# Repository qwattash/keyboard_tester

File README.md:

# Components for testing an early prototype RGB backlit keyboard

The design is based on the atmega32u4 MCU, found on teensey boards and arduino Leonardo boards, and an ISSI 3733 led driver that can drive leds for half of a full-size keyboard.

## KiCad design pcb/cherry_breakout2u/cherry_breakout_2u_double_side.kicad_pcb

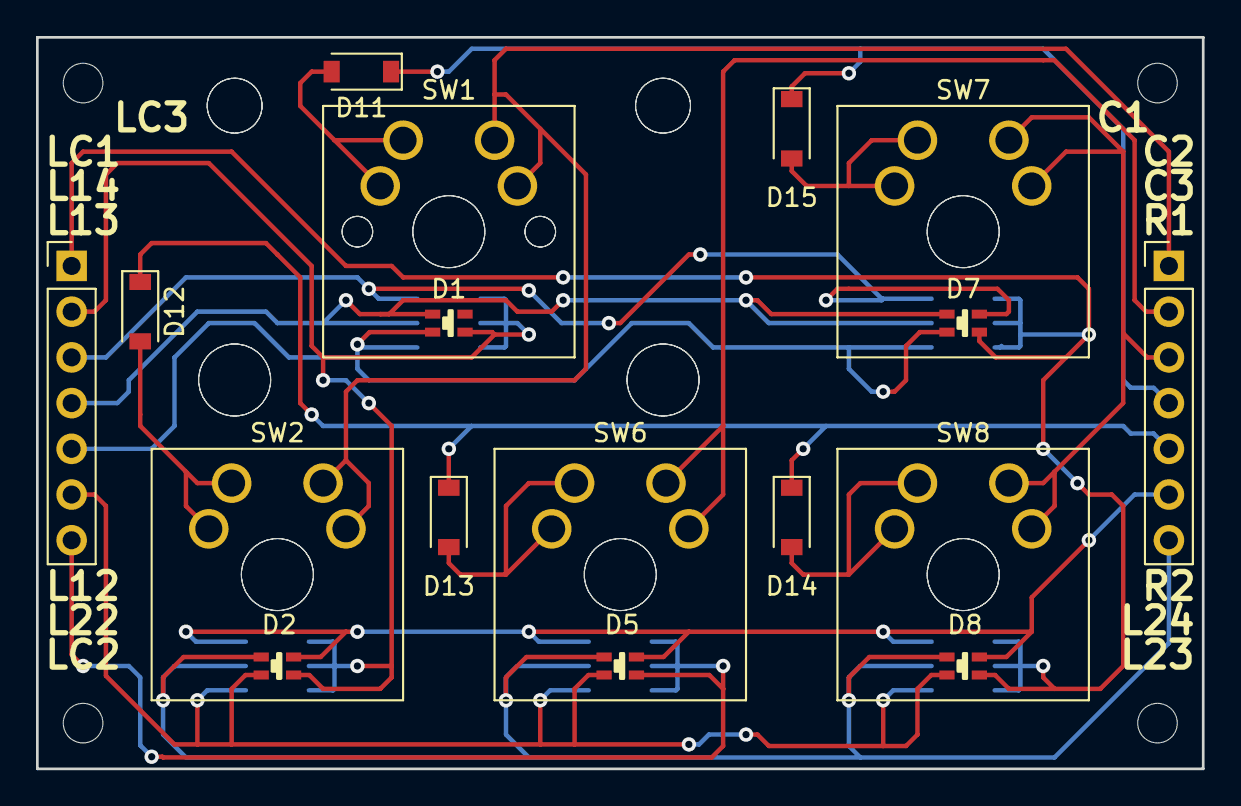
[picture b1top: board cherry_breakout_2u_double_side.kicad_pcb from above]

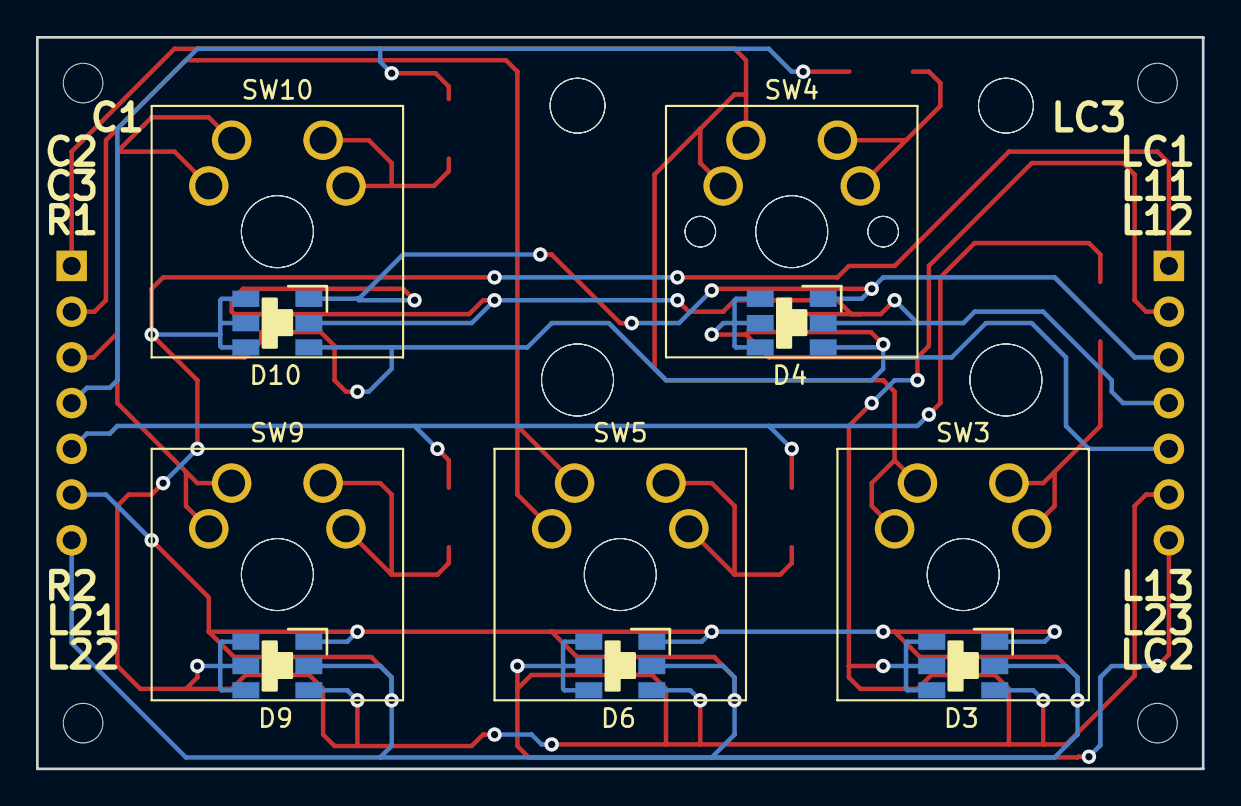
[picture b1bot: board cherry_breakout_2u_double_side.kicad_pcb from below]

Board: 2 copper layers, 64.8 x 40.6 mm, 27 parts (10 on the bottom side), 19 nets.

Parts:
D1: LED_A; Led_SMD_0606
D2: LED_C; Led_SMD_0606
D3: LED_Cb; LED_smd_1214
D4: LED_Ab; LED_smd_1214
D5: LED_D; Led_SMD_0606
D6: LED_Db; LED_smd_1214
D7: LED_B; Led_SMD_0606
D8: LED_E; Led_SMD_0606
D9: LED_Eb; LED_smd_1214
D10: LED_Bb; LED_smd_1214
D11: D_A; D_SOD-123
D12: D_C; D_SOD-123
D13: D_D; D_SOD-123
D14: D_E; D_SOD-123
D15: D_B; D_SOD-123
J1: ConnLeft; Pin_Header_Straight_1x07_Pitch2.54mm
J2: ConnRight; Pin_Header_Straight_1x07_Pitch2.54mm
SW1: A; SW_Cherry_MX1A_2.00u_PCB
SW2: C; SW_Cherry_MX1A_1.00u_Plate
SW3: Cb; SW_Cherry_MX1A_1.00u_Plate
SW4: Ab; SW_Cherry_MX1A_2.00u_PCB
SW5: Db; SW_Cherry_MX1A_1.00u_Plate
SW6: D; SW_Cherry_MX1A_1.00u_Plate
SW7: B; SW_Cherry_MX1A_1.00u_Plate
SW8: E; SW_Cherry_MX1A_1.00u_Plate
SW9: Eb; SW_Cherry_MX1A_1.00u_Plate
SW10: Bb; SW_Cherry_MX1A_1.00u_Plate

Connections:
unnamed: D1.1, D2.1, D3.4, D3.5, D3.6, D4.4, D4.5, D4.6, J1.2
unnamed: D1.2, D4.3, D7.2, D10.3, J1.5
unnamed: D1.3, D4.2, D7.3, D10.2, J1.4
unnamed: D1.4, D4.1, D7.4, D10.1, J1.3
unnamed: D2.2, D3.3, D5.2, D6.3, D8.2, D9.3, J1.6
unnamed: D2.3, D3.2, D5.3, D6.2, D8.3, D9.2, J2.7
unnamed: D2.4, D3.1, D5.4, D6.1, D8.4, D9.1, J2.6
unnamed: D5.1, D6.4, D6.5, D6.6, J1.7
unnamed: D7.1, D8.1, D9.4, D9.5, D9.6, D10.4, D10.5, D10.6, J1.1
unnamed: D11.1, D15.1, J2.4
unnamed: D11.2, SW1.2, SW4.1
unnamed: D12.1, D13.1, D14.1, J2.5
unnamed: D12.2, SW2.2, SW3.1
unnamed: D13.2, SW5.1, SW6.2
unnamed: D14.2, SW8.2, SW9.1
unnamed: D15.2, SW7.2, SW10.1
unnamed: J2.1, SW1.1, SW2.1, SW3.2, SW4.2
unnamed: J2.2, SW5.2, SW6.1
unnamed: J2.3, SW7.1, SW8.1, SW9.2, SW10.2

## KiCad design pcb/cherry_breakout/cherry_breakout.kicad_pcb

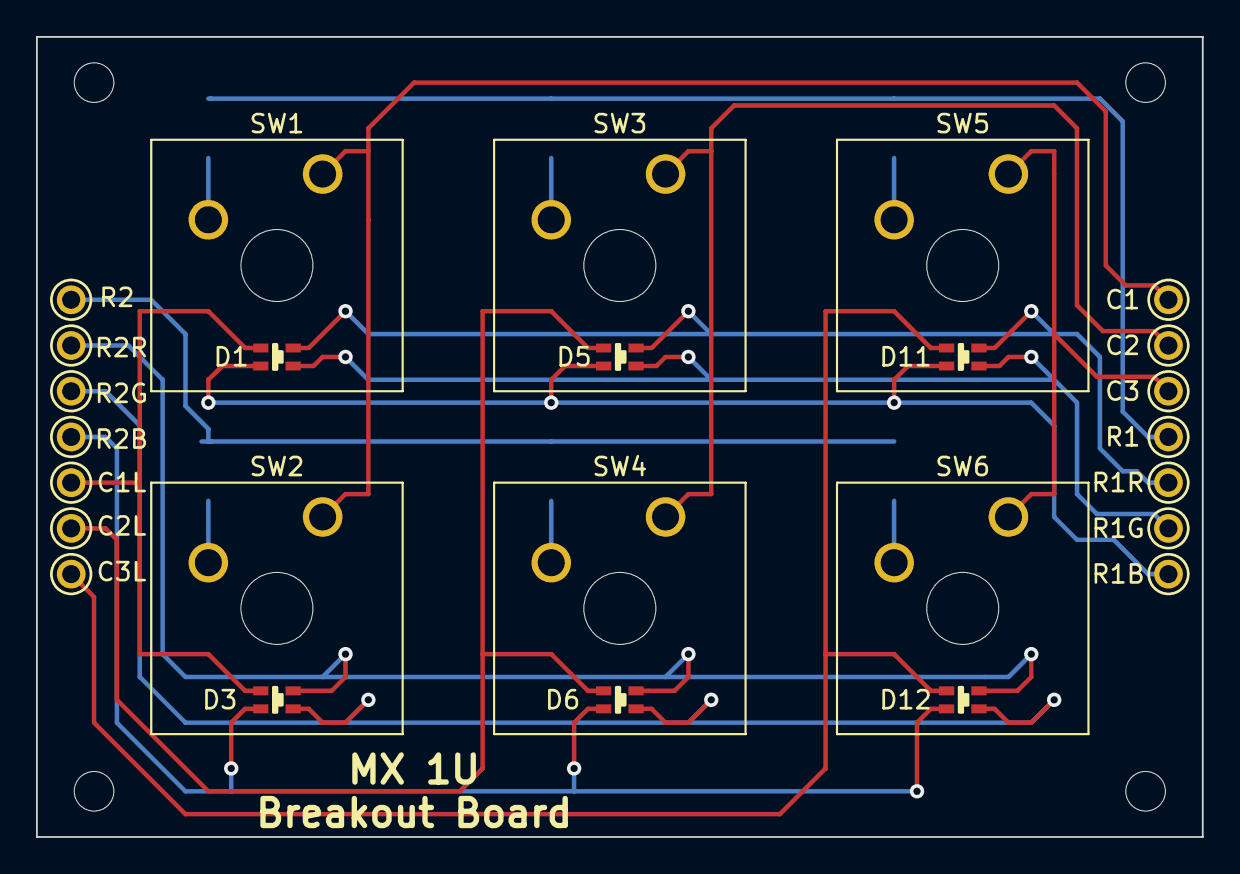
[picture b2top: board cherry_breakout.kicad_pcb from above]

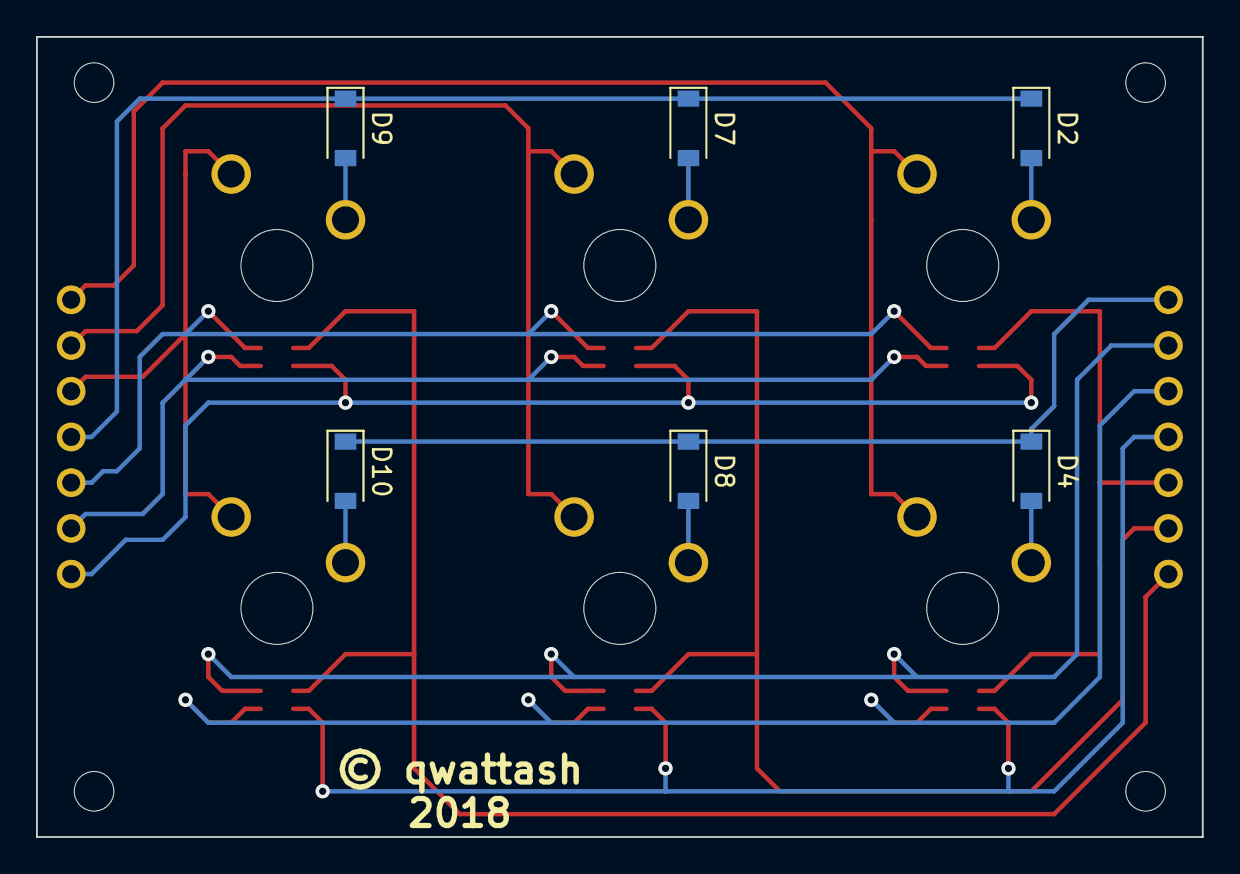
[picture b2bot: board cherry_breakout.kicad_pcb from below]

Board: 2 copper layers, 64.8 x 44.5 mm, 32 parts (6 on the bottom side), 20 nets.

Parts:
C1: Col1; Connector_Via_1.0mm
C1L: LCol1; Connector_Via_1.0mm
C2: Col2; Connector_Via_1.0mm
C2L: LCol2; Connector_Via_1.0mm
C3: Col3; Connector_Via_1.0mm
C3L: LCol3; Connector_Via_1.0mm
D1: LED_11; Led_SMD_0606
D2, D4, D7, D8, D9, D10: D_ALT; D_SOD-123
D3: LED_21; Led_SMD_0606
D5: LED_12; Led_SMD_0606
D6: LED_22; Led_SMD_0606
D11: LED_13; Led_SMD_0606
D12: LED_23; Led_SMD_0606
R1: Row 1; Connector_Via_1.0mm
R1B: LRow1B; Connector_Via_1.0mm
R1G: LRow1G; Connector_Via_1.0mm
R1R: LRow1R; Connector_Via_1.0mm
R2: Row 2; Connector_Via_1.0mm
R2B: LRow2B; Connector_Via_1.0mm
R2G: LRow2G; Connector_Via_1.0mm
R2R: LRow2R; Connector_Via_1.0mm
SW1: SW11; SW_Cherry_MX1A_1.00u_Plate
SW2: SW21; SW_Cherry_MX1A_1.00u_Plate
SW3: SW12; SW_Cherry_MX1A_1.00u_Plate
SW4: SW22; SW_Cherry_MX1A_1.00u_Plate
SW5: SW13; SW_Cherry_MX1A_1.00u_Plate
SW6: SW23; SW_Cherry_MX1A_1.00u_Plate

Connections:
unnamed: C1L.1, D1.1, D3.1
unnamed: D1.2, D5.2, D11.2, R1R.1
unnamed: D1.3, D5.3, D11.3, R1G.1
unnamed: D1.4, D5.4, D11.4, R1B.1
unnamed: D2.1, D7.1, D9.1, R1.1
unnamed: D2.2, SW1.2
unnamed: D4.2, SW2.2
unnamed: C2L.1, D5.1, D6.1
unnamed: D7.2, SW3.2
unnamed: D8.2, SW4.2
unnamed: D9.2, SW5.2
unnamed: D4.1, D8.1, D10.1, R2.1
unnamed: D10.2, SW6.2
unnamed: C3L.1, D11.1, D12.1
unnamed: D3.2, D6.2, D12.2, R2R.1
unnamed: D3.3, D6.3, D12.3, R2G.1
unnamed: D3.4, D6.4, D12.4, R2B.1
unnamed: C1.1, SW1.1, SW2.1
unnamed: C2.1, SW3.1, SW4.1
unnamed: C3.1, SW5.1, SW6.1

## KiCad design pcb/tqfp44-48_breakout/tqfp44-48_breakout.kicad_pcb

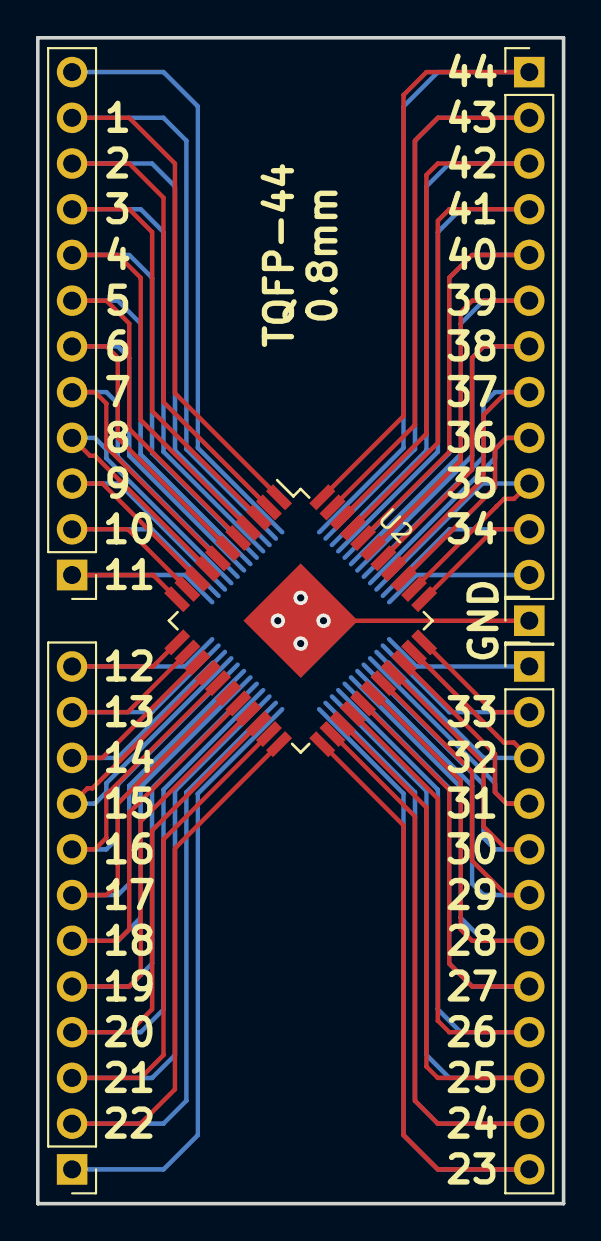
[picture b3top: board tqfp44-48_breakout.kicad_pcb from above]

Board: 2 copper layers, 29.2 x 64.8 mm, 7 parts (1 on the bottom side), 49 nets.

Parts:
J1, J2, J3, J4: Conn_01x12; Pin_Header_Straight_1x12_Pitch2.54mm
J5: Conn_01x01; Pin_Header_Straight_1x01_Pitch2.54mm
U1: Generic_48pin_with_pad; TQFP-48-1EP_7x7mm_Pitch0.5mm
U2: Generic_44pin_with_pad; TQFP-44-1EP_10x10mm_Pitch0.8mm

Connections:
GND: J5.1, U1.49, U2.45
unnamed: J1.1, U1.37
unnamed: J1.2, U1.38, U2.22
unnamed: J1.3, U1.39, U2.21
unnamed: J1.4, U1.40, U2.20
unnamed: J1.5, U1.41, U2.19
unnamed: J1.6, U1.42, U2.18
unnamed: J1.7, U1.43, U2.17
unnamed: J1.8, U1.44, U2.16
unnamed: J1.9, U1.45, U2.15
unnamed: J1.10, U1.46, U2.14
unnamed: J1.11, U1.47, U2.13
unnamed: J1.12, U1.48, U2.12
unnamed: J2.1, U1.1, U2.11
unnamed: J2.2, U1.2, U2.10
unnamed: J2.3, U1.3, U2.9
unnamed: J2.4, U1.4, U2.8
unnamed: J2.5, U1.5, U2.7
unnamed: J2.6, U1.6, U2.6
unnamed: J2.7, U1.7, U2.5
unnamed: J2.8, U1.8, U2.4
unnamed: J2.9, U1.9, U2.3
unnamed: J2.10, U1.10, U2.2
unnamed: J2.11, U1.11, U2.1
unnamed: J2.12, U1.12
unnamed: J3.1, U1.25
unnamed: J3.2, U1.26, U2.33
unnamed: J3.3, U1.27, U2.32
unnamed: J3.4, U1.28, U2.31
unnamed: J3.5, U1.29, U2.30
unnamed: J3.6, U1.30, U2.29
unnamed: J3.7, U1.31, U2.28
unnamed: J3.8, U1.32, U2.27
unnamed: J3.9, U1.33, U2.26
unnamed: J3.10, U1.34, U2.25
unnamed: J3.11, U1.35, U2.24
unnamed: J3.12, U1.36, U2.23
unnamed: J4.1, U1.13, U2.44
unnamed: J4.2, U1.14, U2.43
unnamed: J4.3, U1.15, U2.42
unnamed: J4.4, U1.16, U2.41
unnamed: J4.5, U1.17, U2.40
unnamed: J4.6, U1.18, U2.39
unnamed: J4.7, U1.19, U2.38
unnamed: J4.8, U1.20, U2.37
unnamed: J4.9, U1.21, U2.36
unnamed: J4.10, U1.22, U2.35
unnamed: J4.11, U1.23, U2.34
unnamed: J4.12, U1.24

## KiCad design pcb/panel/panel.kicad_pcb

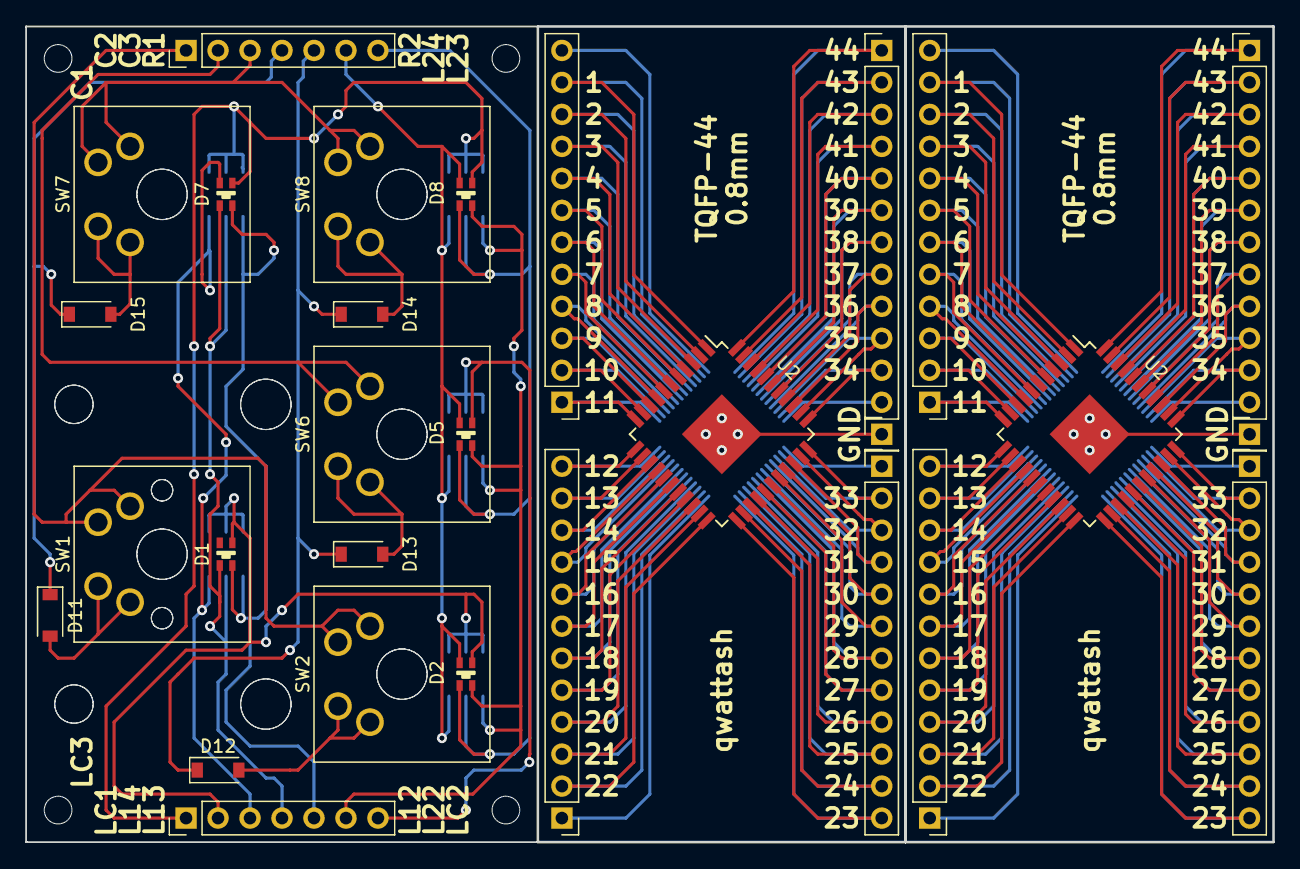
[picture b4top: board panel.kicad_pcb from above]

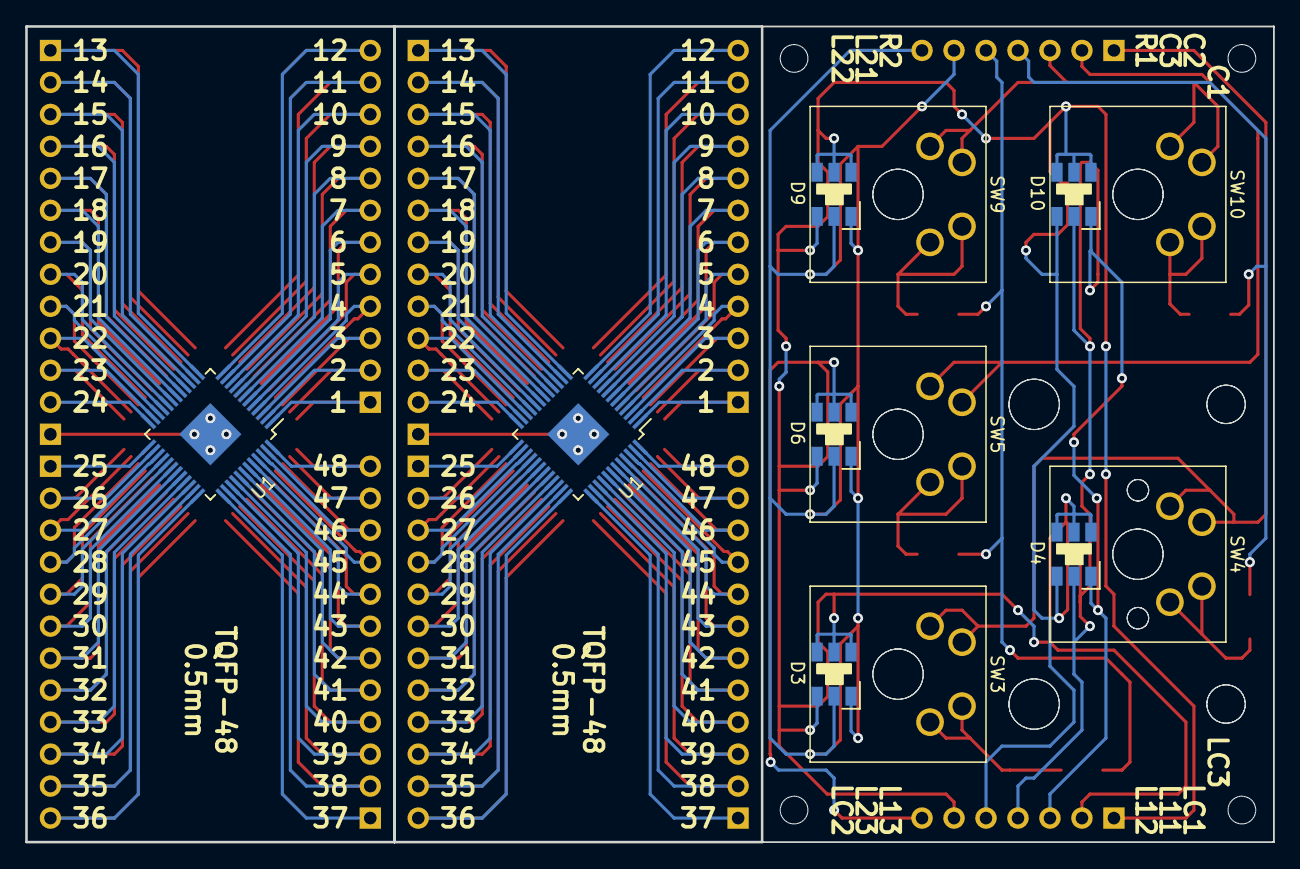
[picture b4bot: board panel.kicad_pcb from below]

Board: 2 copper layers, 99.1 x 64.8 mm, 41 parts (12 on the bottom side), 65 nets.

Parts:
D1: LED_A; Led_SMD_0606
D2: LED_C; Led_SMD_0606
D3: LED_Cb; LED_smd_1214
D4: LED_Ab; LED_smd_1214
D5: LED_D; Led_SMD_0606
D6: LED_Db; LED_smd_1214
D7: LED_B; Led_SMD_0606
D8: LED_E; Led_SMD_0606
D9: LED_Eb; LED_smd_1214
D10: LED_Bb; LED_smd_1214
D11: D_A; D_SOD-123
D12: D_C; D_SOD-123
D13: D_D; D_SOD-123
D14: D_E; D_SOD-123
D15: D_B; D_SOD-123
J1, J1#2, J2, J2#2, J3, J3#2, J4, J4#2: Conn_01x12; Pin_Header_Straight_1x12_Pitch2.54mm
J1#3: ConnLeft; Pin_Header_Straight_1x07_Pitch2.54mm
J2#3: ConnRight; Pin_Header_Straight_1x07_Pitch2.54mm
J5, J5#2: Conn_01x01; Pin_Header_Straight_1x01_Pitch2.54mm
SW1: A; SW_Cherry_MX1A_2.00u_PCB
SW2: C; SW_Cherry_MX1A_1.00u_Plate
SW3: Cb; SW_Cherry_MX1A_1.00u_Plate
SW4: Ab; SW_Cherry_MX1A_2.00u_PCB
SW5: Db; SW_Cherry_MX1A_1.00u_Plate
SW6: D; SW_Cherry_MX1A_1.00u_Plate
SW7: B; SW_Cherry_MX1A_1.00u_Plate
SW8: E; SW_Cherry_MX1A_1.00u_Plate
SW9: Eb; SW_Cherry_MX1A_1.00u_Plate
SW10: Bb; SW_Cherry_MX1A_1.00u_Plate
U1, U1#2: Generic_48pin_with_pad; TQFP-48-1EP_7x7mm_Pitch0.5mm
U2, U2#2: Generic_44pin_with_pad; TQFP-44-1EP_10x10mm_Pitch0.8mm

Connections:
GND: J5.1, J5#2.1, U1.49, U1#2.49, U2.45, U2#2.45
unnamed: D1.1, D2.1, D3.4, D3.5, D3.6, D4.4, D4.5, D4.6, J1#3.2
unnamed: D1.2, D4.3, D7.2, D10.3, J1#3.5
unnamed: D1.3, D4.2, D7.3, D10.2, J1#3.4
unnamed: D1.4, D4.1, D7.4, D10.1, J1#3.3
unnamed: D2.2, D3.3, D5.2, D6.3, D8.2, D9.3, J1#3.6
unnamed: D2.3, D3.2, D5.3, D6.2, D8.3, D9.2, J2#3.7
unnamed: D2.4, D3.1, D5.4, D6.1, D8.4, D9.1, J2#3.6
unnamed: D5.1, D6.4, D6.5, D6.6, J1#3.7
unnamed: D7.1, D8.1, D9.4, D9.5, D9.6, D10.4, D10.5, D10.6, J1#3.1
unnamed: D11.1, D15.1, J2#3.4
unnamed: D11.2, SW1.2, SW4.1
unnamed: D12.1, D13.1, D14.1, J2#3.5
unnamed: D12.2, SW2.2, SW3.1
unnamed: D13.2, SW5.1, SW6.2
unnamed: D14.2, SW8.2, SW9.1
unnamed: D15.2, SW7.2, SW10.1
unnamed: J1.1, J1#2.1, U1.37, U1#2.37
unnamed: J1.2, J1#2.2, U1.38, U1#2.38, U2.22, U2#2.22
unnamed: J1.3, J1#2.3, U1.39, U1#2.39, U2.21, U2#2.21
unnamed: J1.4, J1#2.4, U1.40, U1#2.40, U2.20, U2#2.20
unnamed: J1.5, J1#2.5, U1.41, U1#2.41, U2.19, U2#2.19
unnamed: J1.6, J1#2.6, U1.42, U1#2.42, U2.18, U2#2.18
unnamed: J1.7, J1#2.7, U1.43, U1#2.43, U2.17, U2#2.17
unnamed: J1.8, J1#2.8, U1.44, U1#2.44, U2.16, U2#2.16
unnamed: J1.9, J1#2.9, U1.45, U1#2.45, U2.15, U2#2.15
unnamed: J1.10, J1#2.10, U1.46, U1#2.46, U2.14, U2#2.14
unnamed: J1.11, J1#2.11, U1.47, U1#2.47, U2.13, U2#2.13
unnamed: J1.12, J1#2.12, U1.48, U1#2.48, U2.12, U2#2.12
unnamed: J2.1, J2#2.1, J2#3.1, SW1.1, SW2.1, SW3.2, SW4.2, U1.1, U1#2.1, U2.11, U2#2.11
unnamed: J2.2, J2#2.2, J2#3.2, SW5.2, SW6.1, U1.2, U1#2.2, U2.10, U2#2.10
unnamed: J2.3, J2#2.3, J2#3.3, SW7.1, SW8.1, SW9.2, SW10.2, U1.3, U1#2.3, U2.9, U2#2.9
unnamed: J2.4, J2#2.4, U1.4, U1#2.4, U2.8, U2#2.8
unnamed: J2.5, J2#2.5, U1.5, U1#2.5, U2.7, U2#2.7
unnamed: J2.6, J2#2.6, U1.6, U1#2.6, U2.6, U2#2.6
unnamed: J2.7, J2#2.7, U1.7, U1#2.7, U2.5, U2#2.5
unnamed: J2.8, J2#2.8, U1.8, U1#2.8, U2.4, U2#2.4
unnamed: J2.9, J2#2.9, U1.9, U1#2.9, U2.3, U2#2.3
unnamed: J2.10, J2#2.10, U1.10, U1#2.10, U2.2, U2#2.2
unnamed: J2.11, J2#2.11, U1.11, U1#2.11, U2.1, U2#2.1
unnamed: J2.12, J2#2.12, U1.12, U1#2.12
unnamed: J3.1, J3#2.1, U1.25, U1#2.25
unnamed: J3.2, J3#2.2, U1.26, U1#2.26, U2.33, U2#2.33
unnamed: J3.3, J3#2.3, U1.27, U1#2.27, U2.32, U2#2.32
unnamed: J3.4, J3#2.4, U1.28, U1#2.28, U2.31, U2#2.31
unnamed: J3.5, J3#2.5, U1.29, U1#2.29, U2.30, U2#2.30
unnamed: J3.6, J3#2.6, U1.30, U1#2.30, U2.29, U2#2.29
unnamed: J3.7, J3#2.7, U1.31, U1#2.31, U2.28, U2#2.28
unnamed: J3.8, J3#2.8, U1.32, U1#2.32, U2.27, U2#2.27
unnamed: J3.9, J3#2.9, U1.33, U1#2.33, U2.26, U2#2.26
unnamed: J3.10, J3#2.10, U1.34, U1#2.34, U2.25, U2#2.25
unnamed: J3.11, J3#2.11, U1.35, U1#2.35, U2.24, U2#2.24
unnamed: J3.12, J3#2.12, U1.36, U1#2.36, U2.23, U2#2.23
unnamed: J4.1, J4#2.1, U1.13, U1#2.13, U2.44, U2#2.44
unnamed: J4.2, J4#2.2, U1.14, U1#2.14, U2.43, U2#2.43
unnamed: J4.3, J4#2.3, U1.15, U1#2.15, U2.42, U2#2.42
unnamed: J4.4, J4#2.4, U1.16, U1#2.16, U2.41, U2#2.41
unnamed: J4.5, J4#2.5, U1.17, U1#2.17, U2.40, U2#2.40
unnamed: J4.6, J4#2.6, U1.18, U1#2.18, U2.39, U2#2.39
unnamed: J4.7, J4#2.7, U1.19, U1#2.19, U2.38, U2#2.38
unnamed: J4.8, J4#2.8, U1.20, U1#2.20, U2.37, U2#2.37
unnamed: J4.9, J4#2.9, U1.21, U1#2.21, U2.36, U2#2.36
unnamed: J4.10, J4#2.10, U1.22, U1#2.22, U2.35, U2#2.35
unnamed: J4.11, J4#2.11, U1.23, U1#2.23, U2.34, U2#2.34
unnamed: J4.12, J4#2.12, U1.24, U1#2.24

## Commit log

2018-07-29 Remove arduino-cmake since we are not going to use any arduino stuff. Add lufa submodule.
2018-11-05 Update LUFA version
2018-11-16 Add LUFA build artifacts to gitignore
2018-11-16 Add USB CDC class datasheet
2018-11-16 Add initial hello world implementation of USB serial interface
2018-11-21 Add pull-down resistors on keyboard rows.
2018-12-01 Add generic bitset implementation.
2018-12-01 Move keyboard matrix handling to a separate source file.
    This operates the keyboard scanning loop with the main timer.
    The keyboard record will be fed from the matrix scanning loop, this
    makes it easier to integrate a secondary matrix scanning input over TWI
    at a later point.
2018-12-03 Add USB HID specification.
2018-12-03 Add USB HID Keyboard Interface implementation.
    Basic reporting of key presses now works.
2018-12-03 Move all serial output to a DEBUG macro.
2018-12-06 Add ATTiny 261/461/861 datasheet. Add TWI application note.
2018-12-06 Add secondary keyboard matrix to the schematic.
    The secondary matrix is driven by an ATTiny x61 which has the advantage of
    having I2C pins separate from the SPI programming pins, this makes it easier
    to program it without need for isolation from the ATMega32.
    The single LED driver is used to light the LEDs on the secondary matrix as well
    since this does not seem to have much influence in the final design requirements.
2019-01-27 Add secondary keyboard matrix design.
2019-02-04 Do not disable keyboard scanning when the serial is not connected.
2019-05-04 Add prototype backlight control for is3733.
    LED configuration is triggered when the serial is connected.
2019-06-08 Bind backlight actions to keys.
    Move the backlight control logic in the keyboard matrix handling module.
    Add time to tick conversion logic for timer 3.
2019-06-09 Implement breathing modes for leds.
    Key (1,0) is used to cycle through leds.
    Key (1,1) is used to trigger a scan of all the colors in 0x20 increments on the selected led.
    Key (0,0) is used to trigger a keyboard half scan of all the colors in 0x20 increments.
    Key (0,0) must first be pressed to trigger the open/short detection.

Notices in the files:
pcb/cherry_breakout/cherry_breakout.kicad_pcb:
© qwattash
